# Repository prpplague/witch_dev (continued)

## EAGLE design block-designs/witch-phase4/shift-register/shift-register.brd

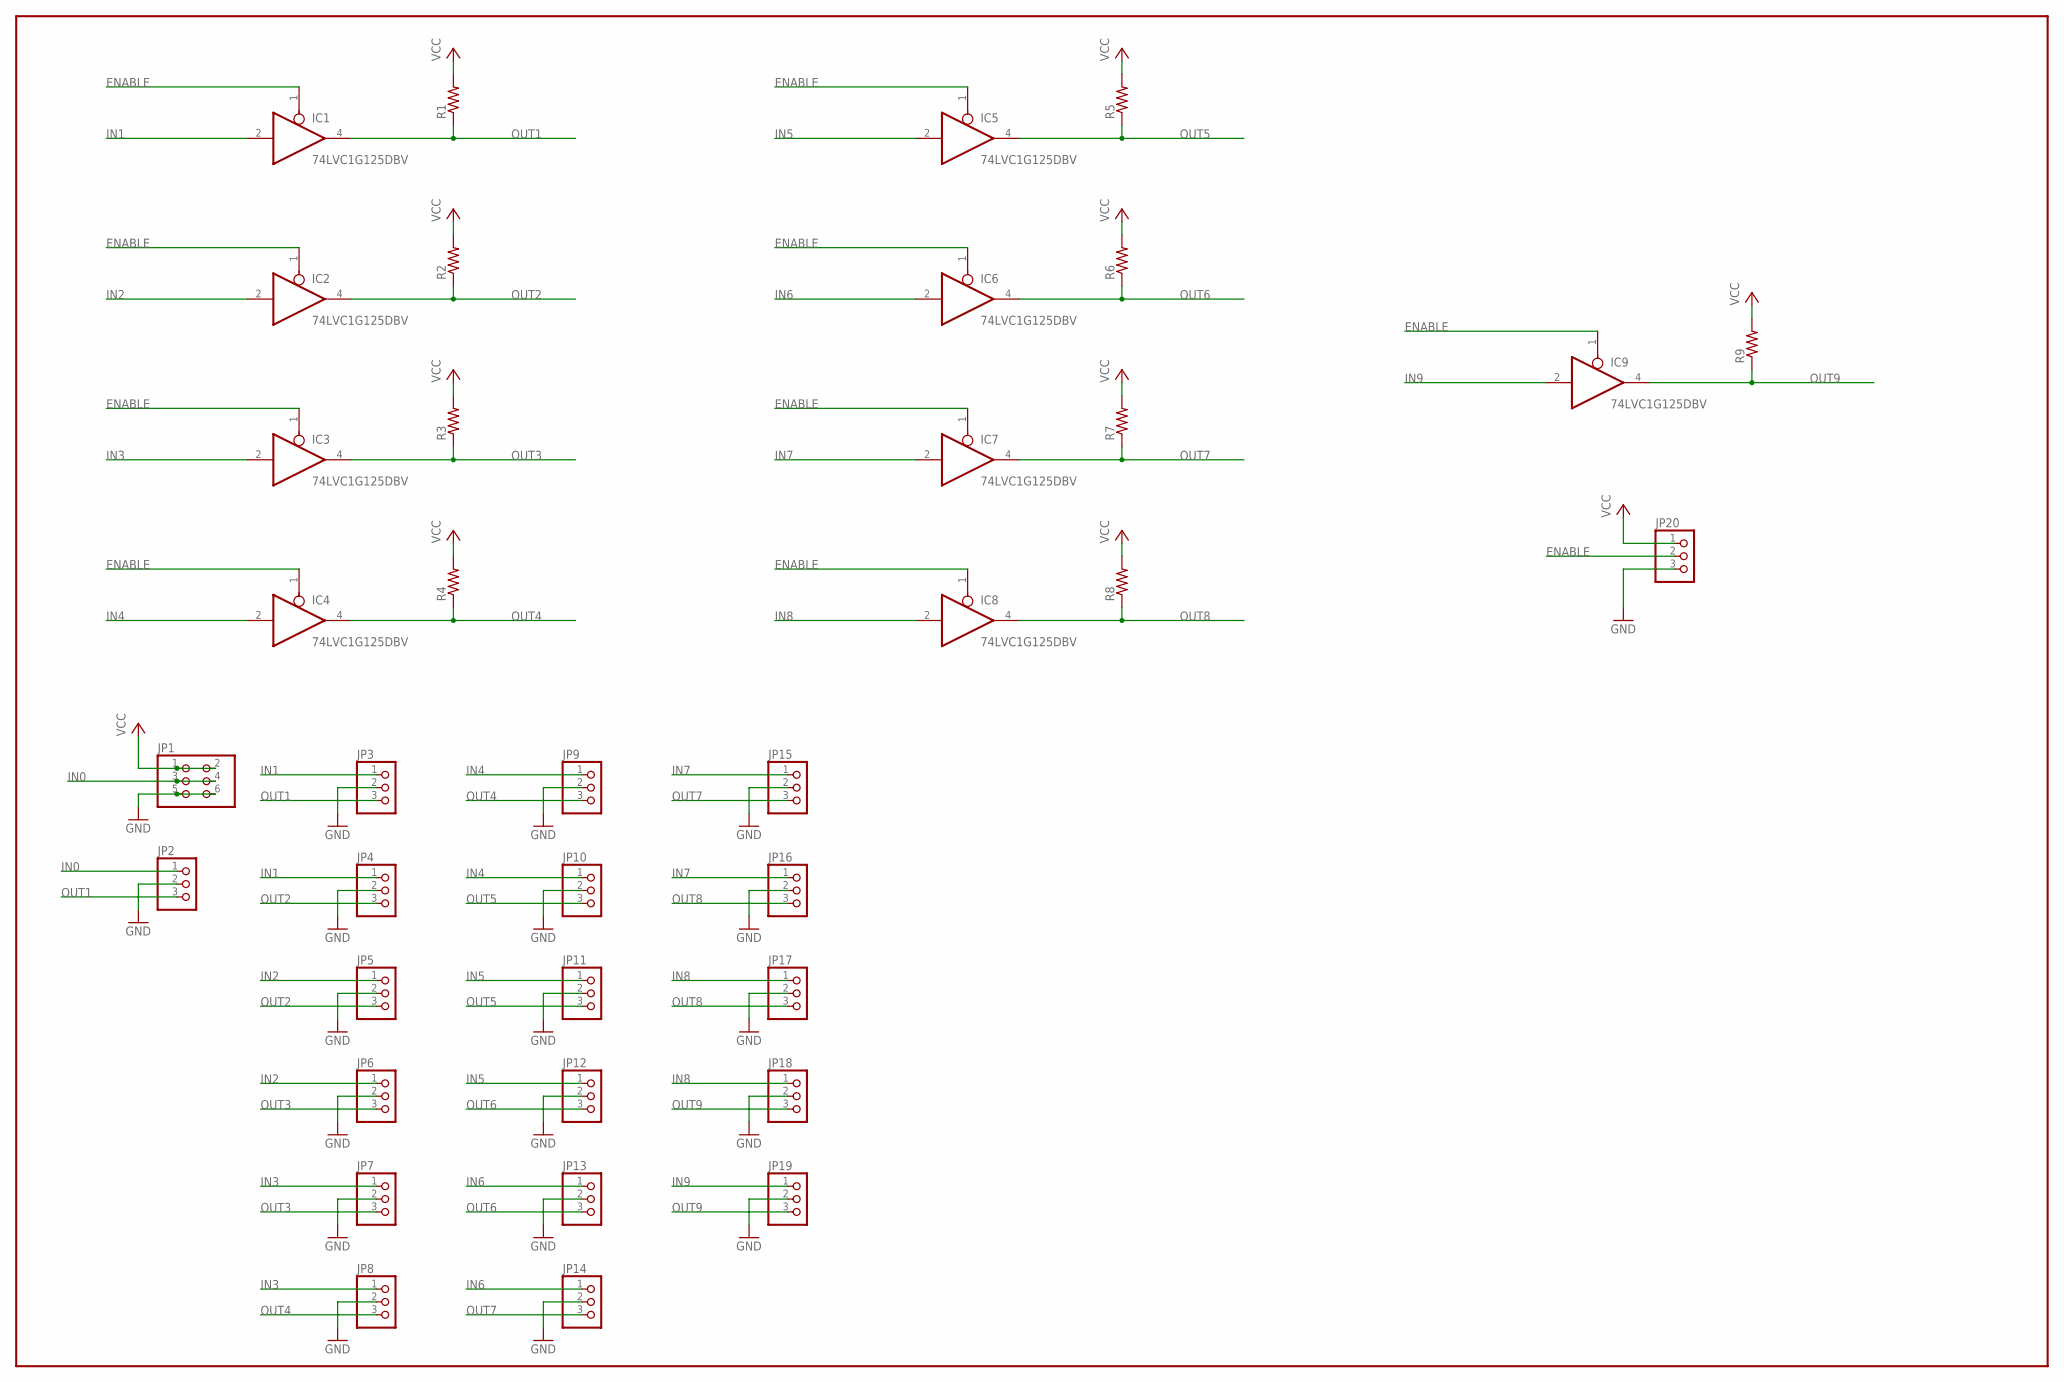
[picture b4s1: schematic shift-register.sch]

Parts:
IC1, IC2, IC3, IC4, IC5, IC6, IC7, IC8, IC9: 74LVC1G125DBV; SOT23-5
JP1: PINHD-2X3; 2X03
JP2, JP3, JP4, JP5, JP6, JP7, JP8, JP9, JP10, JP11, JP12, JP13, JP14, JP15, JP16, JP17, JP18, JP19, JP20: PINHD-1X3; 1X03
R1, R2, R3, R4, R5, R6, R7, R8, R9: R-US_R0603; R0603

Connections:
ENABLE: IC1.1 (OE), IC2.1 (OE), IC3.1 (OE), IC4.1 (OE), IC5.1 (OE), IC6.1 (OE), IC7.1 (OE), IC8.1 (OE), IC9.1 (OE), JP20.2
GND: IC1.3 (GND), IC2.3 (GND), IC3.3 (GND), IC4.3 (GND), IC5.3 (GND), IC6.3 (GND), IC7.3 (GND), IC8.3 (GND), IC9.3 (GND), JP1.5, JP1.6, JP2.2, JP3.2, JP4.2, JP5.2, JP6.2, JP7.2, JP8.2, JP9.2, JP10.2, JP11.2, JP12.2, JP13.2, JP14.2, JP15.2, JP16.2, JP17.2, JP18.2, JP19.2, JP20.3
IN0: JP1.3, JP1.4, JP2.1
IN1: IC1.2 (I), JP3.1, JP4.1
IN2: IC2.2 (I), JP5.1, JP6.1
IN3: IC3.2 (I), JP7.1, JP8.1
IN4: IC4.2 (I), JP9.1, JP10.1
IN5: IC5.2 (I), JP11.1, JP12.1
IN6: IC6.2 (I), JP13.1, JP14.1
IN7: IC7.2 (I), JP15.1, JP16.1
IN8: IC8.2 (I), JP17.1, JP18.1
IN9: IC9.2 (I), JP19.1
OUT1: IC1.4 (O), JP2.3, JP3.3, R1.1
OUT2: IC2.4 (O), JP4.3, JP5.3, R2.1
OUT3: IC3.4 (O), JP6.3, JP7.3, R3.1
OUT4: IC4.4 (O), JP8.3, JP9.3, R4.1
OUT5: IC5.4 (O), JP10.3, JP11.3, R5.1
OUT6: IC6.4 (O), JP12.3, JP13.3, R6.1
OUT7: IC7.4 (O), JP14.3, JP15.3, R7.1
OUT8: IC8.4 (O), JP16.3, JP17.3, R8.1
OUT9: IC9.4 (O), JP18.3, JP19.3, R9.1
VCC: IC1.5 (VCC), IC2.5 (VCC), IC3.5 (VCC), IC4.5 (VCC), IC5.5 (VCC), IC6.5 (VCC), IC7.5 (VCC), IC8.5 (VCC), IC9.5 (VCC), JP1.1, JP1.2, JP20.1, R1.2, R2.2, R3.2, R4.2, R5.2, R6.2, R7.2, R8.2, R9.2

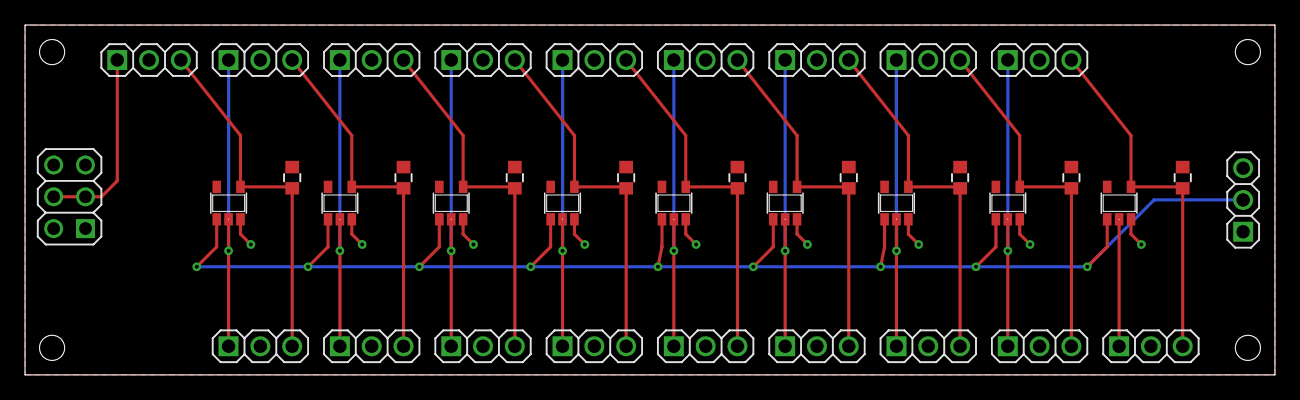
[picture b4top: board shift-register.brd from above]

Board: 2 copper layers, 99.8 x 27.9 mm, 38 parts (0 on the bottom side), 22 nets.

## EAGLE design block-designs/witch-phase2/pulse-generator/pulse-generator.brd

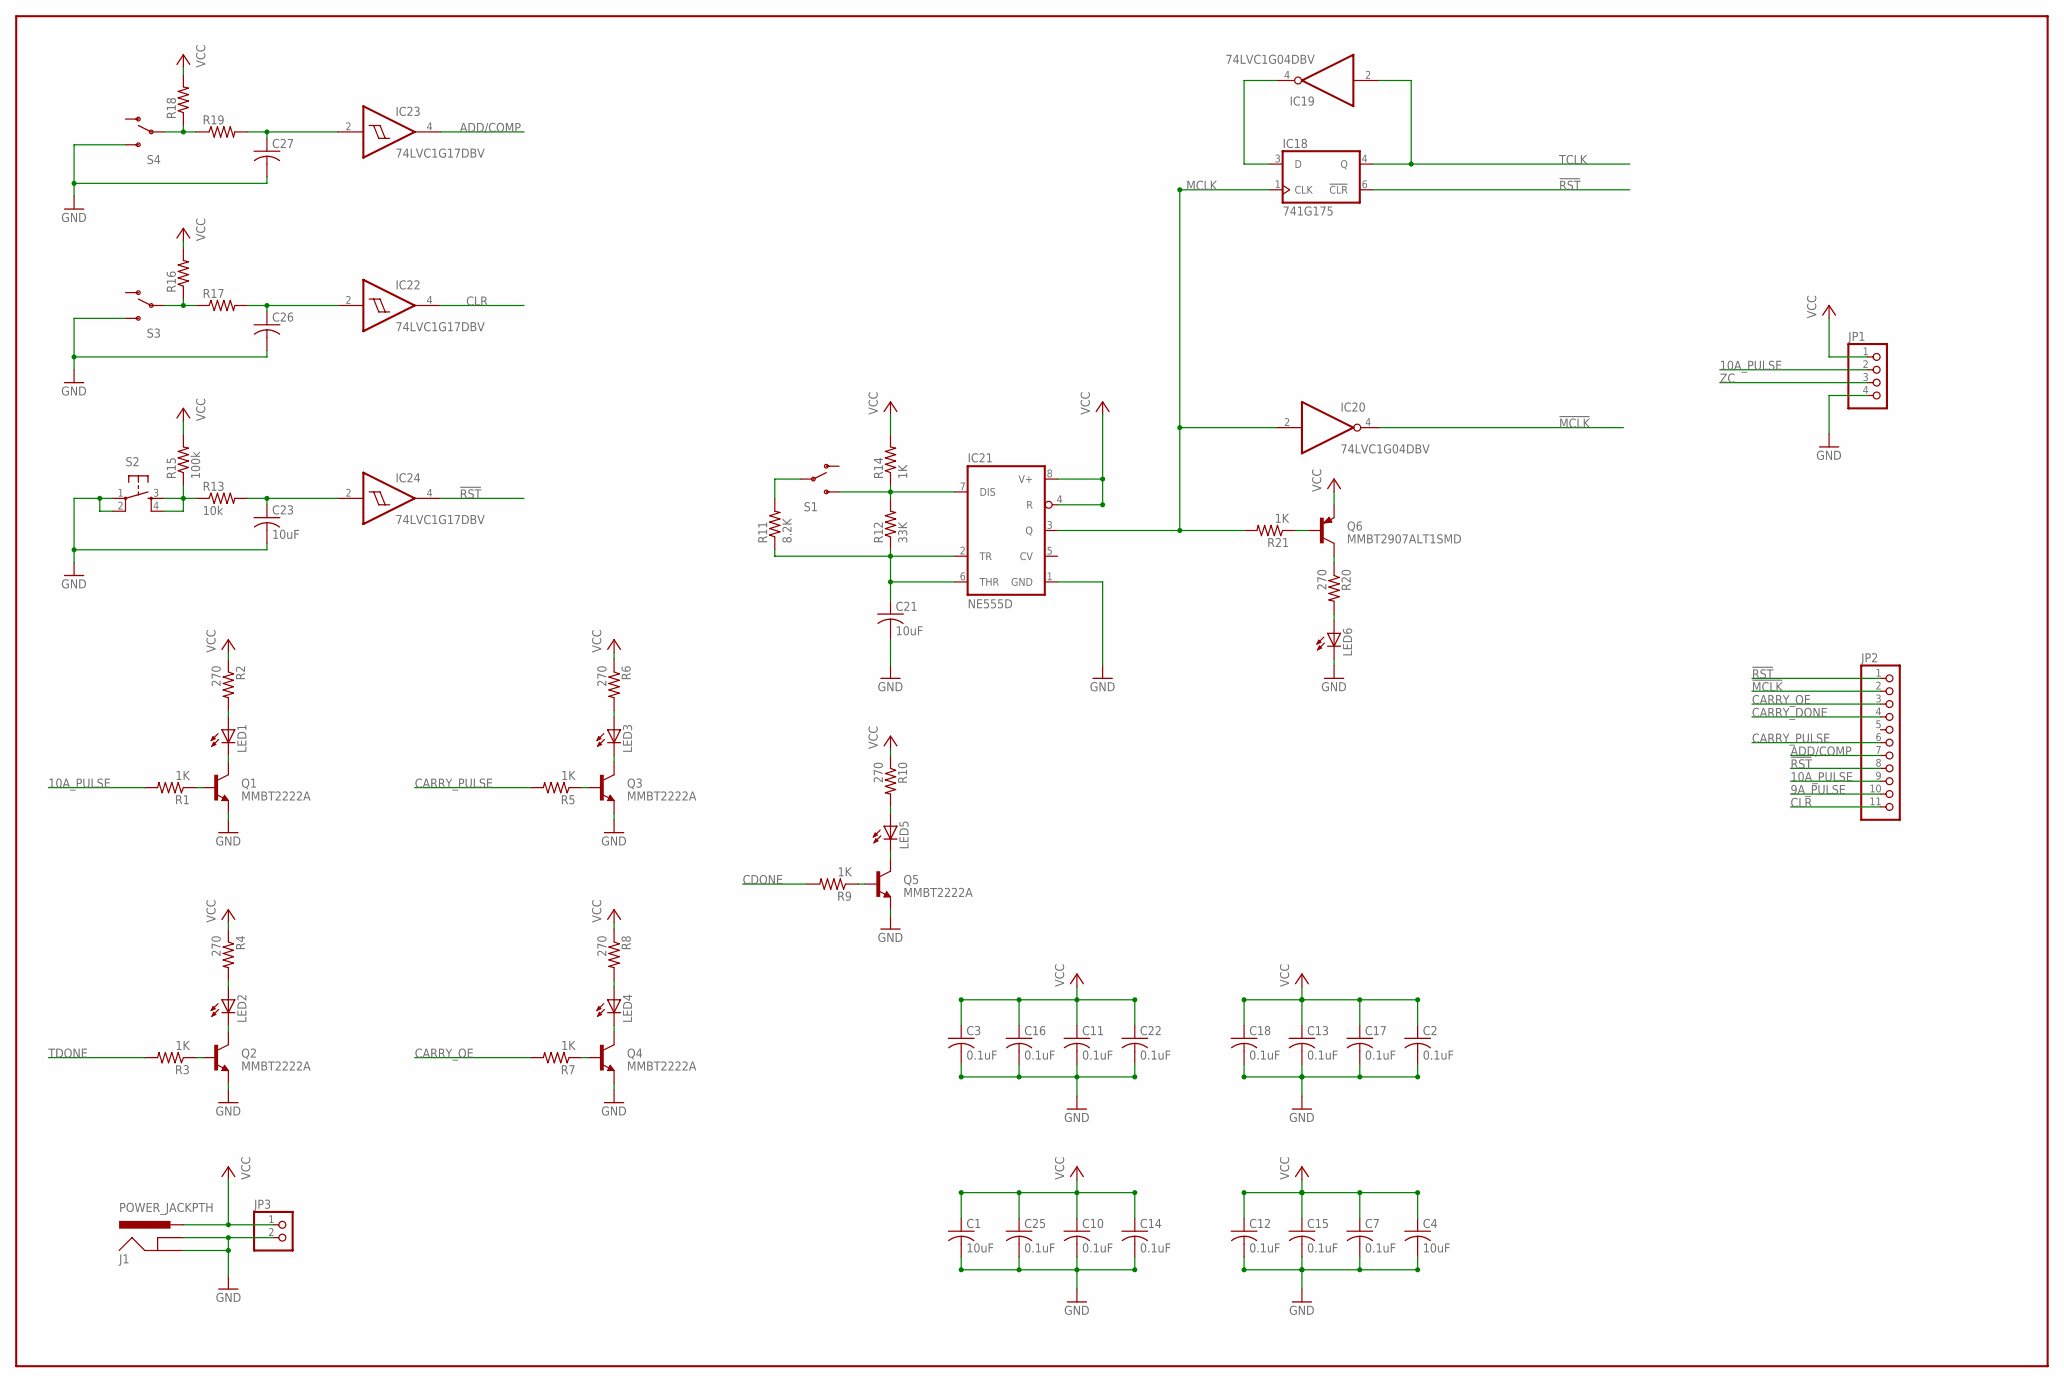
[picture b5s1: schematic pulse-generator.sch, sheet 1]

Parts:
C1, C4, C21, C23: 10uF; C0805
C2, C3, C7, C10, C11, C12, C13, C14, C15, C16, C17, C18, C22, C25: 0.1uF; C0805
C26, C27: C-USC0805; C0805
IC18: 741G175; DBV_R-PDSO-G6
IC19, IC20: 74LVC1G04DBV; SOT23-5
IC21: NE555D; SO08
IC22, IC23, IC24: 74LVC1G17DBV; SOT23-5
J1: POWER_JACKPTH; POWER_JACK_PTH
JP1: PINHD-1X4; 1X04
JP2: PINHD-1X11; 1X11
JP3: PINHD-1X2; 1X02
LED1, LED2, LED3, LED4, LED5, LED6: LEDCHIP-LED0805; CHIP-LED0805
Q1, Q2, Q3, Q4, Q5: MMBT2222A; SOT23-3
Q6: MMBT2907ALT1SMD; SOT23-BEC
R1, R3, R5, R7, R9, R14, R21: 1K; R0805
R2, R4, R6, R8, R10, R20: 270; R0805
R11: 8.2K; R0805
R12: 33K; R0805
R13: 10k; R0805
R15: 100k; R0805
R16, R17, R18, R19: R-US_R0805; R0805
S1, S3, S4: SWITCH-SPDTPTH; SWITCH-SPDT
S2: TAC_SWITCHPTH; TACTILE-PTH

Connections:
9A_PULSE: JP2.10; also elsewhere on the board
10A_PULSE: JP1.2, JP2.9, R1.2; also elsewhere on the board
!MCLK: IC20.4 (O), JP2.2; also elsewhere on the board
!RST: IC18.6 (!CLR), IC24.4 (O), JP2.1, JP2.8; also elsewhere on the board
ADD/COMP: IC23.4 (O), JP2.7
CARRY_DONE: JP2.4; also elsewhere on the board
CARRY_OE: JP2.3, R7.2; also elsewhere on the board
CARRY_PULSE: JP2.6, R5.2; also elsewhere on the board
CDONE: R9.2; also elsewhere on the board
CLR: IC22.4 (O), JP2.11
GND: C1.2, C2.2, C3.2, C4.2, C7.2, C10.2, C11.2, C12.2, C13.2, C14.2, C15.2, C16.2, C17.2, C18.2, C21.2, C22.2, C23.2, C25.2, C26.2, C27.2, IC18.2 (GND), IC19.3 (GND), IC20.3 (GND), IC21.1 (GND), IC22.3 (GND), IC23.3 (GND), IC24.3 (GND), J1.GND, J1.GNDBREAK, JP1.4, JP3.2, LED6.C, Q1.2 (E), Q2.2 (E), Q3.2 (E), Q4.2 (E), Q5.2 (E), S2.1, S2.2, S3.3 (S), S4.3 (S); also elsewhere on the board
MCLK: IC18.1 (CLK), IC20.2 (I), IC21.3 (Q), R21.2
unnamed: IC18.3 (D), IC19.4 (O)
unnamed: C21.1, IC21.2 (TR), IC21.6 (THR), R11.1, R12.1
unnamed: IC21.7 (DIS), R12.2, R14.1, S1.3 (S)
unnamed: R11.2, S1.2
unnamed: Q6.B, R21.1
unnamed: Q6.C, R20.1
unnamed: LED6.A, R20.2
unnamed: LED3.C, Q3.3 (C)
unnamed: LED1.C, Q1.3 (C)
unnamed: C23.1, IC24.2 (I), R13.2
unnamed: R13.1, R15.1, S2.3, S2.4
unnamed: C26.1, IC22.2 (I), R17.2
unnamed: R16.1, R17.1, S3.2
unnamed: Q3.1 (B), R5.1
unnamed: LED3.A, R6.2
unnamed: Q1.1 (B), R1.1
unnamed: LED1.A, R2.2
unnamed: C27.1, IC23.2 (I), R19.2
unnamed: R18.1, R19.1, S4.2
unnamed: LED2.C, Q2.3 (C)
unnamed: Q2.1 (B), R3.1
unnamed: LED2.A, R4.2
unnamed: LED4.C, Q4.3 (C)
unnamed: Q4.1 (B), R7.1
unnamed: LED4.A, R8.2
unnamed: LED5.C, Q5.3 (C)
unnamed: Q5.1 (B), R9.1
unnamed: LED5.A, R10.2
TCLK: IC18.4 (Q), IC19.2 (I); also elsewhere on the board
TDONE: R3.2; also elsewhere on the board
VCC: C1.1, C2.1, C3.1, C4.1, C7.1, C10.1, C11.1, C12.1, C13.1, C14.1, C15.1, C16.1, C17.1, C18.1, C22.1, C25.1, IC18.5 (VCC), IC19.5 (VCC), IC20.5 (VCC), IC21.4 (R), IC21.8 (V+), IC22.5 (VCC), IC23.5 (VCC), IC24.5 (VCC), J1.PWR, JP1.1, JP3.1, Q6.E, R2.1, R4.1, R6.1, R8.1, R10.1, R14.2, R15.2, R16.2, R18.2; also elsewhere on the board
ZC: JP1.3; also elsewhere on the board

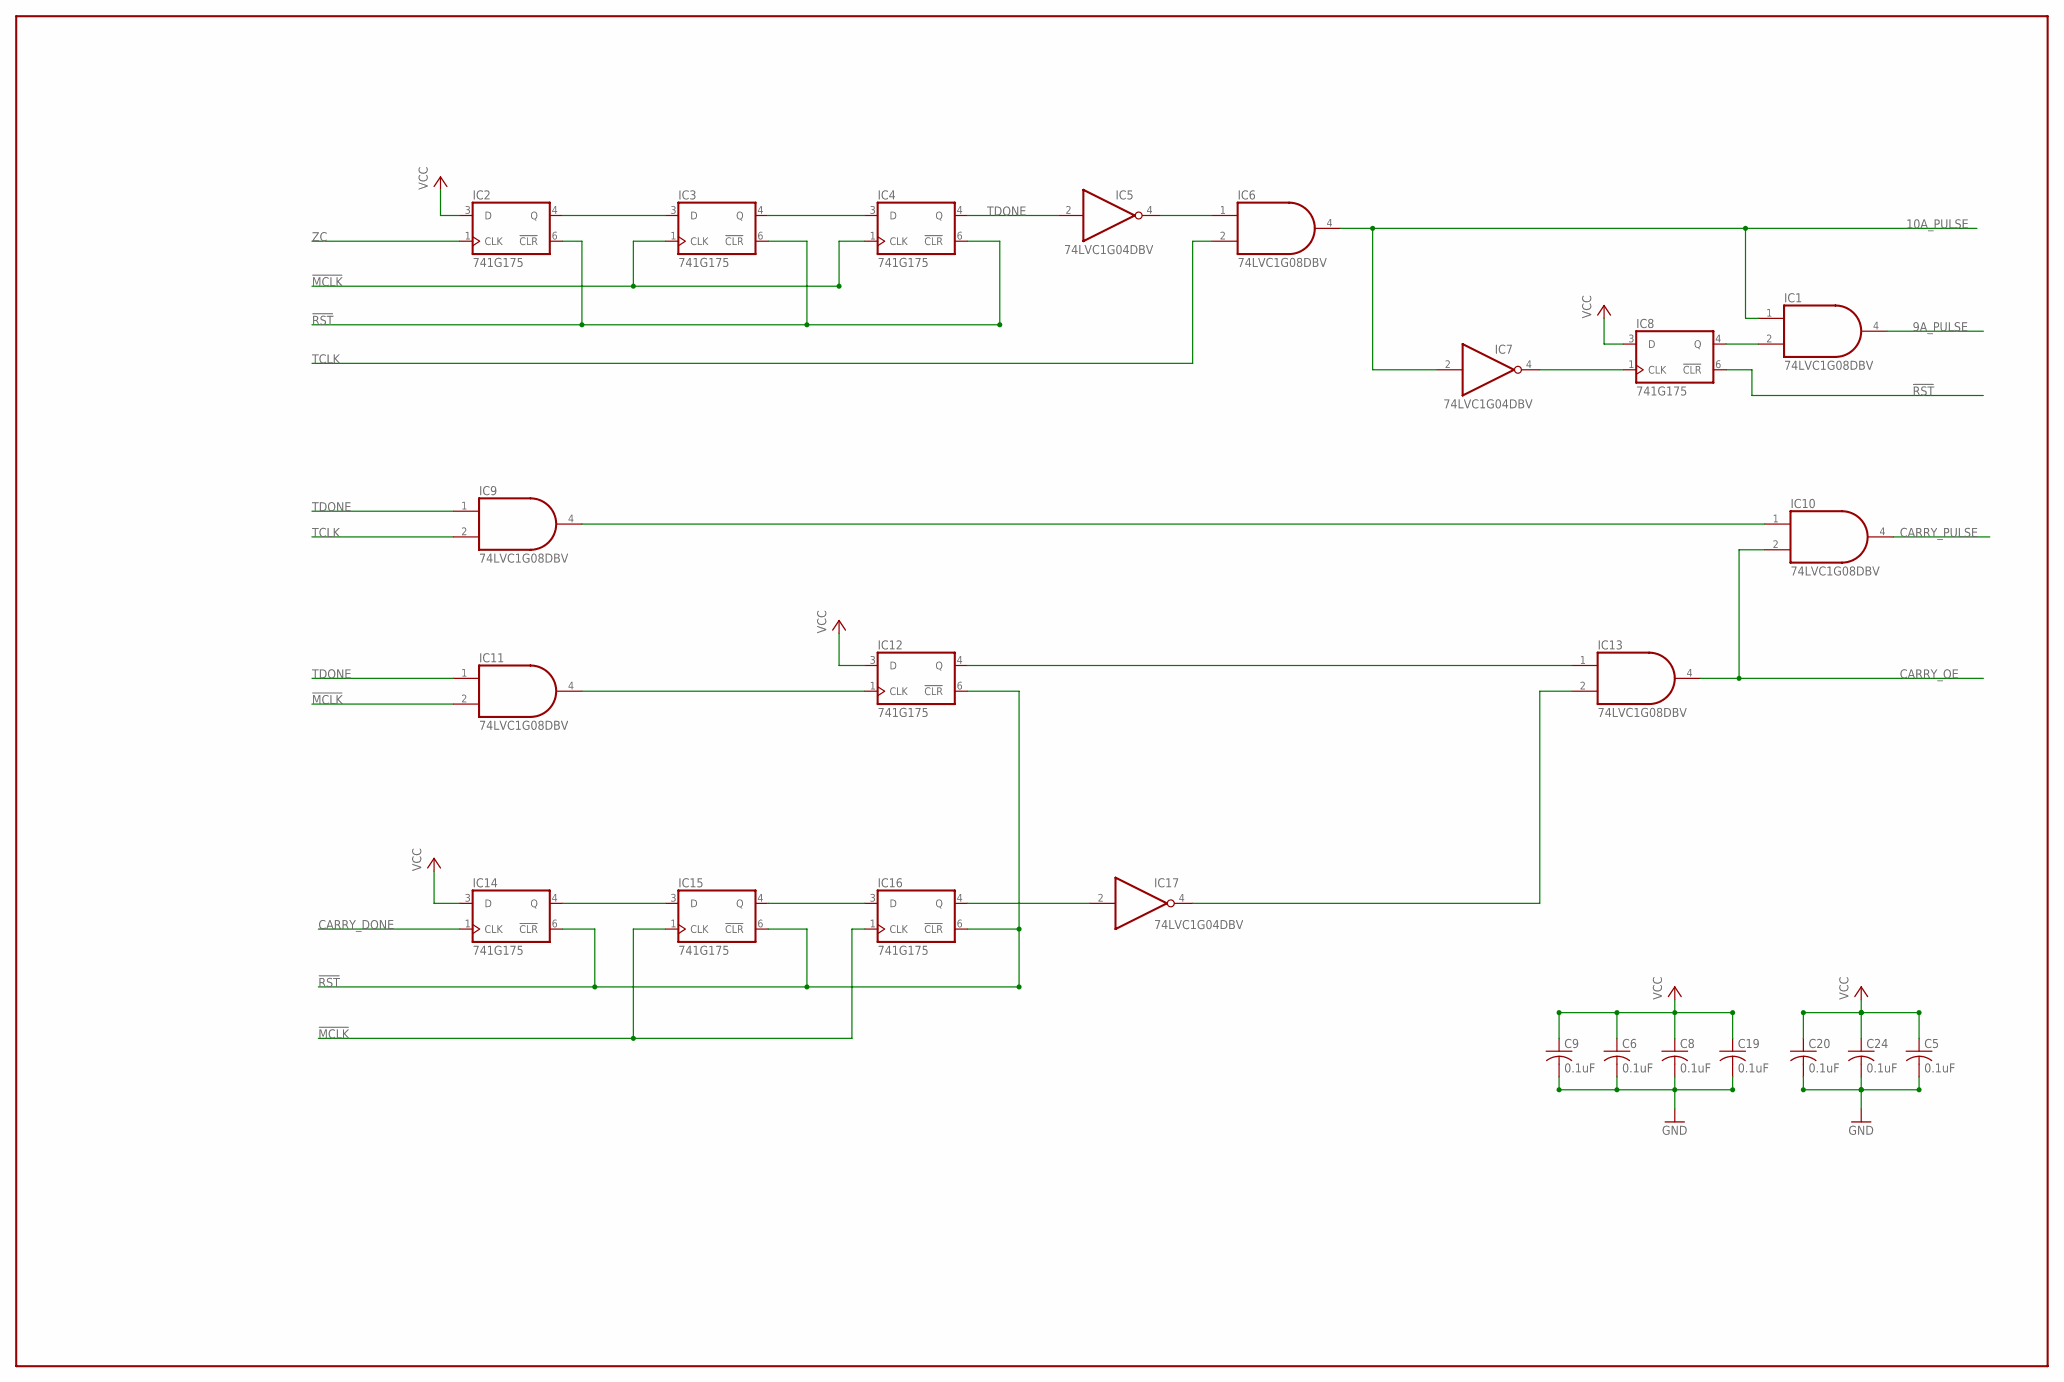
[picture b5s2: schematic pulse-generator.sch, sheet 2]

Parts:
C5, C6, C8, C9, C19, C20, C24: 0.1uF; C0805
IC1, IC6, IC9, IC10, IC11, IC13: 74LVC1G08DBV; SOT23-5
IC2, IC3, IC4, IC8, IC12, IC14, IC15, IC16: 741G175; DBV_R-PDSO-G6
IC5, IC7, IC17: 74LVC1G04DBV; SOT23-5

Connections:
9A_PULSE: IC1.4 (O); also elsewhere on the board
10A_PULSE: IC1.1 (I0), IC6.4 (O), IC7.2 (I); also elsewhere on the board
!CDONE: IC13.2 (I1), IC17.4 (O)
!MCLK: IC3.1 (CLK), IC4.1 (CLK), IC11.2 (I1), IC15.1 (CLK), IC16.1 (CLK); also elsewhere on the board
!RST: IC2.6 (!CLR), IC3.6 (!CLR), IC4.6 (!CLR), IC8.6 (!CLR), IC12.6 (!CLR), IC14.6 (!CLR), IC15.6 (!CLR), IC16.6 (!CLR); also elsewhere on the board
!TDONE: IC5.4 (O), IC6.1 (I0)
CARRY_DONE: IC14.1 (CLK); also elsewhere on the board
CARRY_OE: IC10.2 (I1), IC13.4 (O); also elsewhere on the board
CARRY_PULSE: IC10.4 (O); also elsewhere on the board
CDONE: IC16.4 (Q), IC17.2 (I); also elsewhere on the board
GND: C5.2, C6.2, C8.2, C9.2, C19.2, C20.2, C24.2, IC1.3 (GND), IC2.2 (GND), IC3.2 (GND), IC4.2 (GND), IC5.3 (GND), IC6.3 (GND), IC7.3 (GND), IC8.2 (GND), IC9.3 (GND), IC10.3 (GND), IC11.3 (GND), IC12.2 (GND), IC13.3 (GND), IC14.2 (GND), IC15.2 (GND), IC16.2 (GND), IC17.3 (GND); also elsewhere on the board
unnamed: IC2.4 (Q), IC3.3 (D)
unnamed: IC9.4 (O), IC10.1 (I0)
unnamed: IC14.4 (Q), IC15.3 (D)
unnamed: IC1.2 (I1), IC8.4 (Q)
unnamed: IC3.4 (Q), IC4.3 (D)
unnamed: IC12.4 (Q), IC13.1 (I0)
unnamed: IC11.4 (O), IC12.1 (CLK)
unnamed: IC15.4 (Q), IC16.3 (D)
unnamed: IC7.4 (O), IC8.1 (CLK)
TCLK: IC6.2 (I1), IC9.2 (I1); also elsewhere on the board
TDONE: IC4.4 (Q), IC5.2 (I), IC9.1 (I0), IC11.1 (I0); also elsewhere on the board
VCC: C5.1, C6.1, C8.1, C9.1, C19.1, C20.1, C24.1, IC1.5 (VCC), IC2.3 (D), IC2.5 (VCC), IC3.5 (VCC), IC4.5 (VCC), IC5.5 (VCC), IC6.5 (VCC), IC7.5 (VCC), IC8.3 (D), IC8.5 (VCC), IC9.5 (VCC), IC10.5 (VCC), IC11.5 (VCC), IC12.3 (D), IC12.5 (VCC), IC13.5 (VCC), IC14.3 (D), IC14.5 (VCC), IC15.5 (VCC), IC16.5 (VCC), IC17.5 (VCC); also elsewhere on the board
ZC: IC2.1 (CLK); also elsewhere on the board

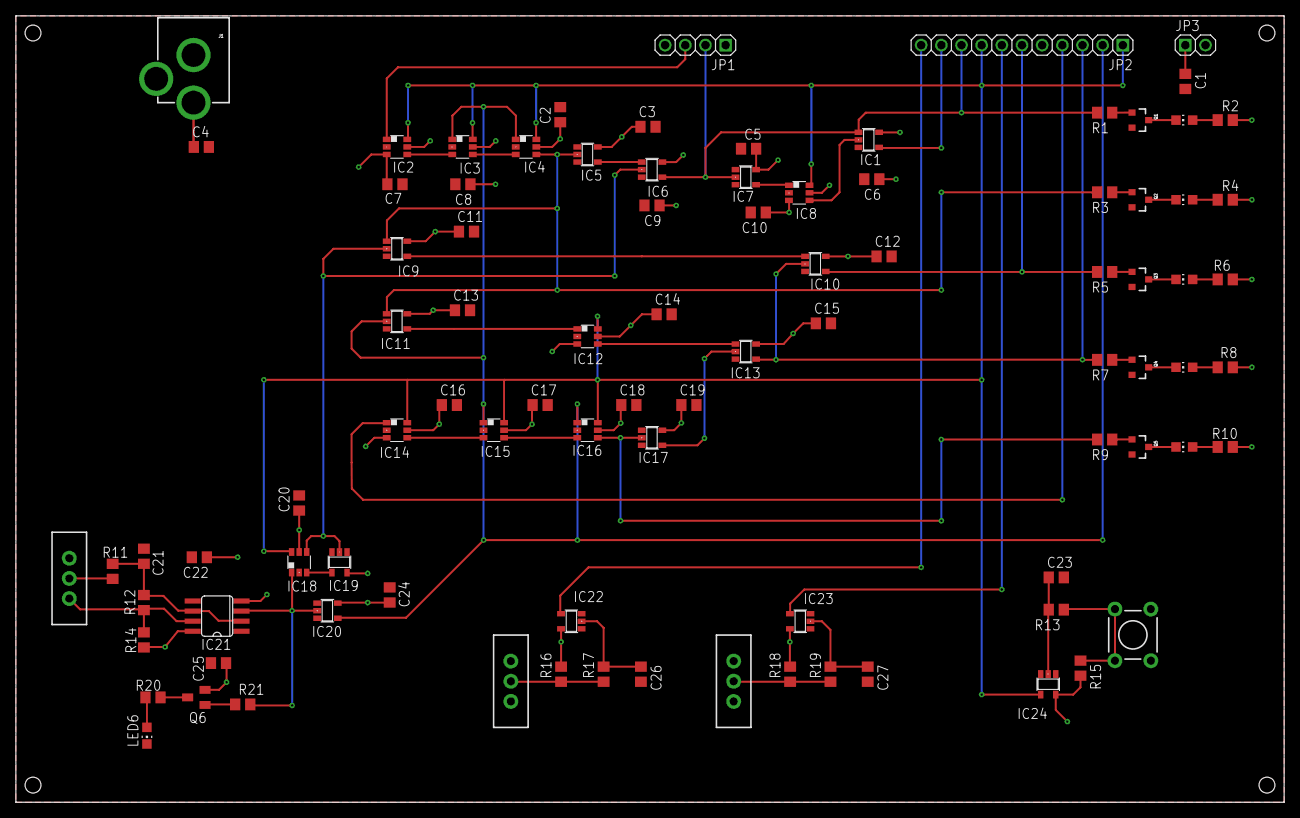
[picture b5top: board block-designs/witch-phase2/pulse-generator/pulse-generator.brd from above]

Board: 2 copper layers, 159.8 x 99.1 mm, 92 parts (0 on the bottom side), 55 nets.

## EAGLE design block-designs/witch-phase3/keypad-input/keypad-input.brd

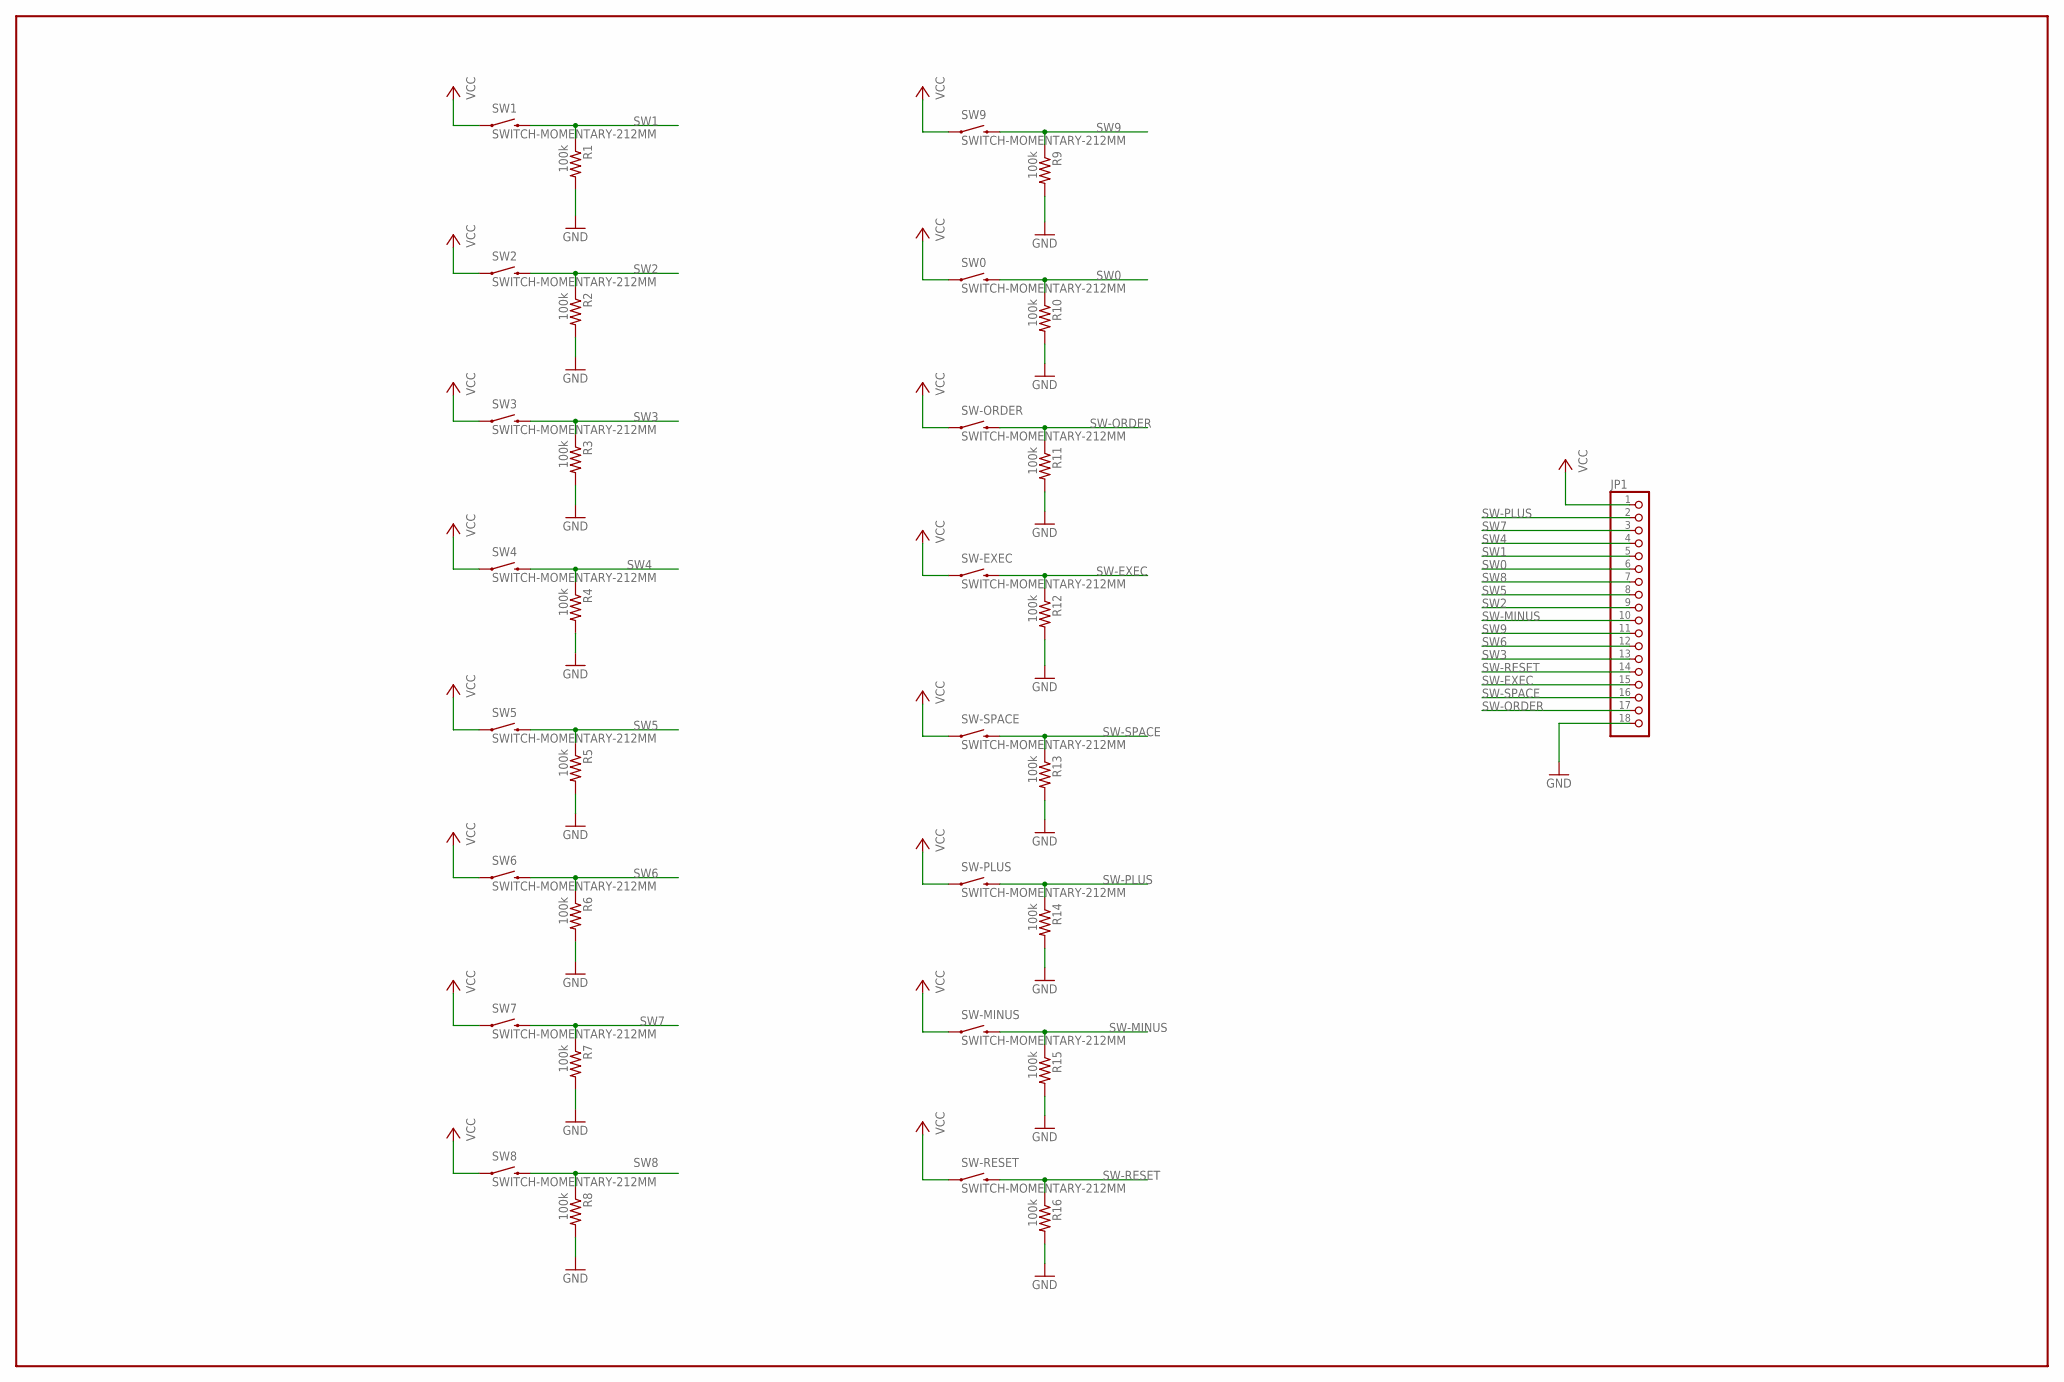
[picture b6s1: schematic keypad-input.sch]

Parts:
JP1: PINHD-1X18; 1X18
R1, R2, R3, R4, R5, R6, R7, R8, R9, R10, R11, R12, R13, R14, R15, R16: 100k; R0805
SW0, SW1, SW2, SW3, SW4, SW5, SW6, SW7, SW8, SW9: SWITCH-MOMENTARY-212MM; TACTILE-PTH-12MM
SW-EXEC: SWITCH-MOMENTARY-212MM; TACTILE-PTH-12MM
SW-MINUS: SWITCH-MOMENTARY-212MM; TACTILE-PTH-12MM
SW-ORDER: SWITCH-MOMENTARY-212MM; TACTILE-PTH-12MM
SW-PLUS: SWITCH-MOMENTARY-212MM; TACTILE-PTH-12MM
SW-RESET: SWITCH-MOMENTARY-212MM; TACTILE-PTH-12MM
SW-SPACE: SWITCH-MOMENTARY-212MM; TACTILE-PTH-12MM

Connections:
GND: JP1.18, R1.2, R2.2, R3.2, R4.2, R5.2, R6.2, R7.2, R8.2, R9.2, R10.2, R11.2, R12.2, R13.2, R14.2, R15.2, R16.2
SW0: JP1.6, R10.1, SW0.3 (2)
SW1: JP1.5, R1.1, SW1.3 (2)
SW2: JP1.9, R2.1, SW2.3 (2)
SW3: JP1.13, R3.1, SW3.3 (2)
SW4: JP1.4, R4.1, SW4.3 (2)
SW5: JP1.8, R5.1, SW5.3 (2)
SW6: JP1.12, R6.1, SW6.3 (2)
SW7: JP1.3, R7.1, SW7.3 (2)
SW8: JP1.7, R8.1, SW8.3 (2)
SW9: JP1.11, R9.1, SW9.3 (2)
SW-EXEC: JP1.15, R12.1, SW-EXEC.3 (2)
SW-MINUS: JP1.10, R15.1, SW-MINUS.3 (2)
SW-ORDER: JP1.17, R11.1, SW-ORDER.3 (2)
SW-PLUS: JP1.2, R14.1, SW-PLUS.3 (2)
SW-RESET: JP1.14, R16.1, SW-RESET.3 (2)
SW-SPACE: JP1.16, R13.1, SW-SPACE.3 (2)
VCC: JP1.1, SW0.1, SW1.1, SW2.1, SW3.1, SW4.1, SW5.1, SW6.1, SW7.1, SW8.1, SW9.1, SW-EXEC.1, SW-MINUS.1, SW-ORDER.1, SW-PLUS.1, SW-RESET.1, SW-SPACE.1

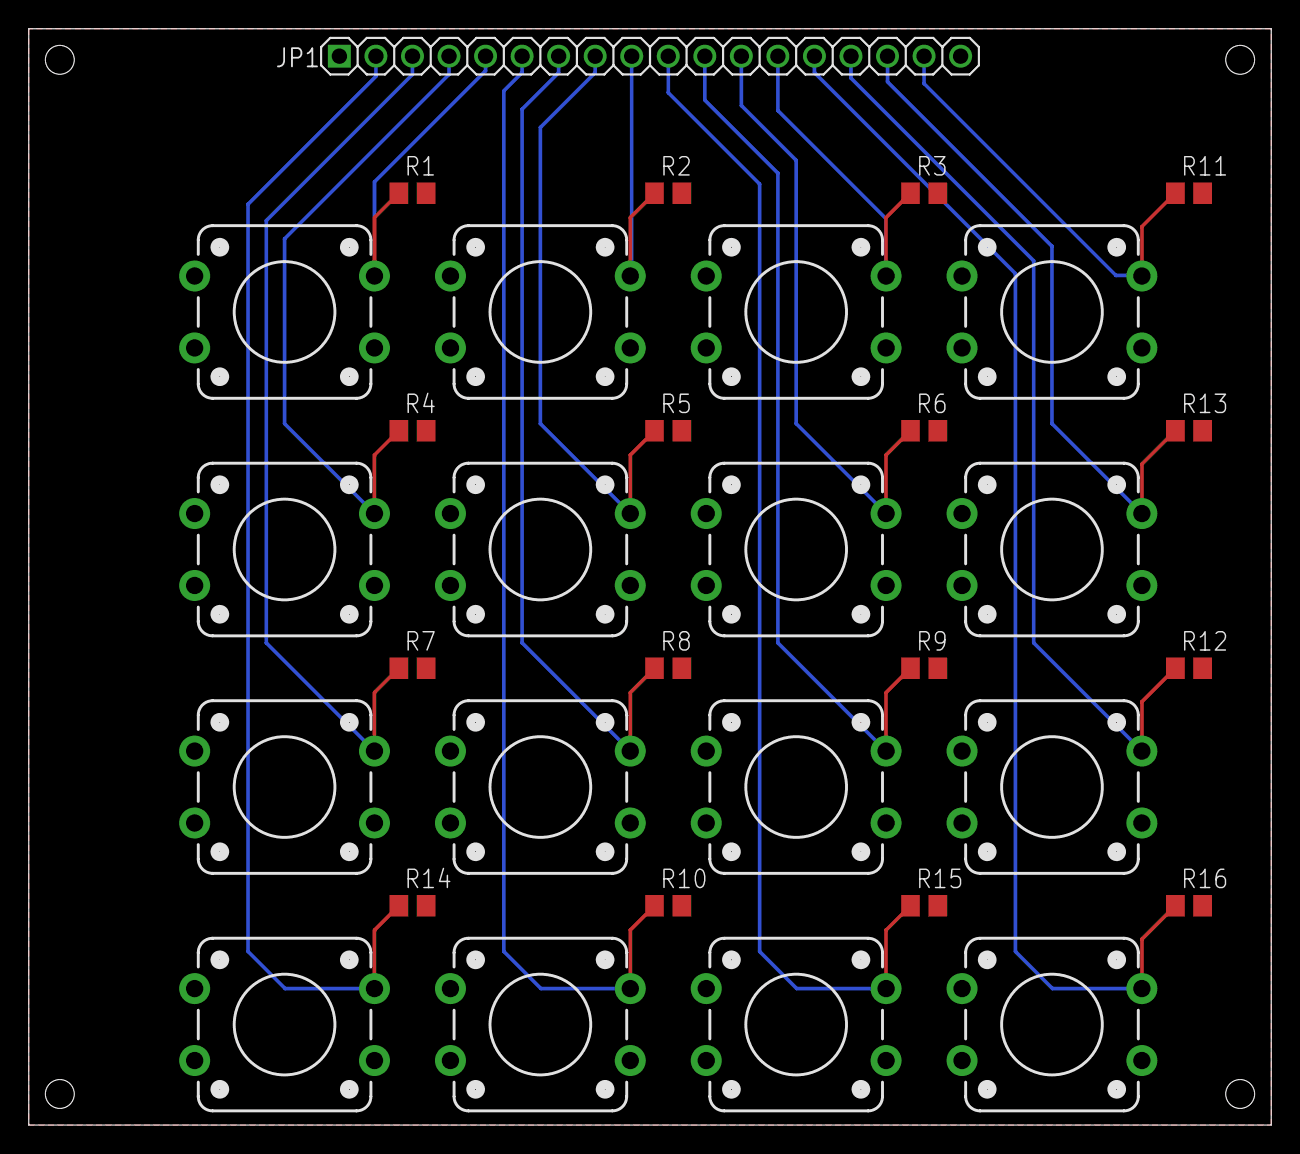
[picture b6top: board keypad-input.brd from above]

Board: 2 copper layers, 86.4 x 76.2 mm, 33 parts (0 on the bottom side), 18 nets.
